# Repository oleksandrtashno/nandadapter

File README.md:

# 360-clip to Xgecu T48/T56 Adapter board
Adapter board to connect solderless TSSOP-56 clip (https://www.360-clip.com/) to Xgecu T48/T56 programmer.

The design was tested and funcitons properly.
## What you need to get it working

1. Xgecu T48/T56 programmer with USB cable
2. Original adapter board (comes with Xgecu programmer)
  NOTE: Now Xgecu programmer comes with different boards that are not compatible with this design, and the one that I have is apparently hard to find now
3. This adapter board with pins and sockets soldered.

Parts 4, 5 and 6 come with 360-clip.

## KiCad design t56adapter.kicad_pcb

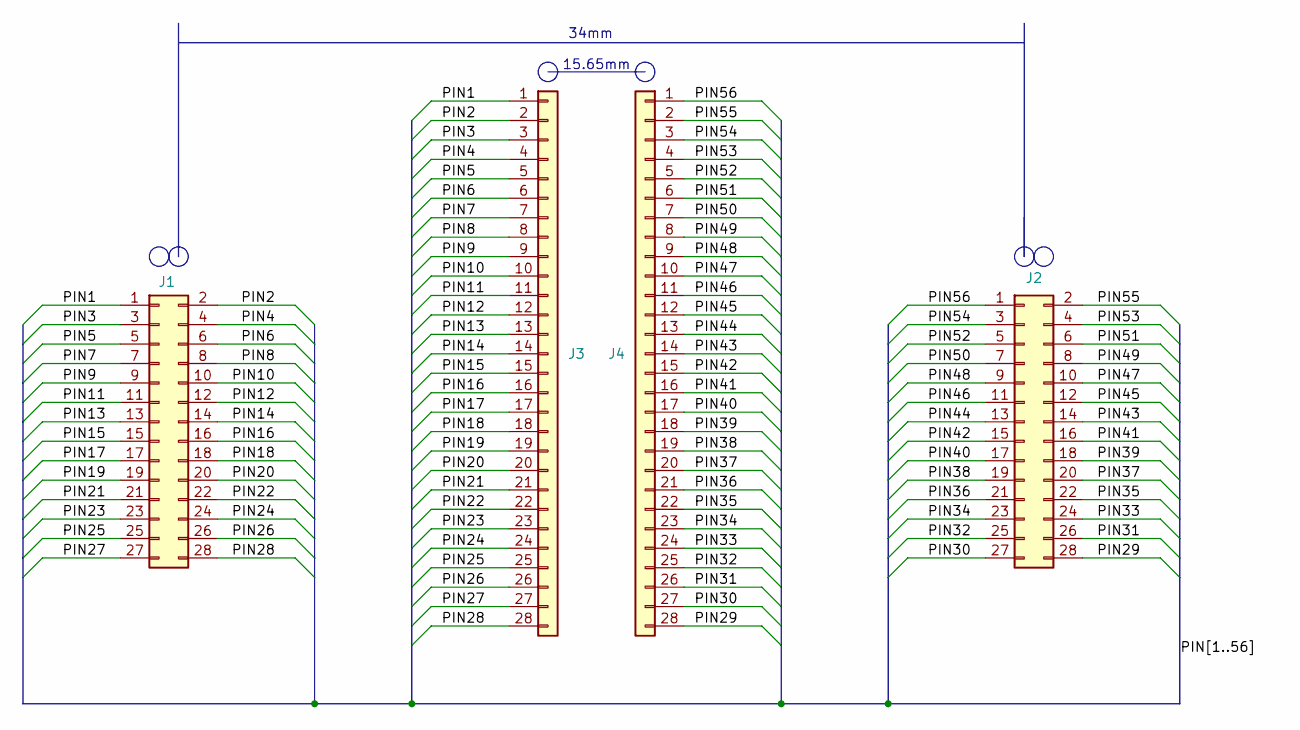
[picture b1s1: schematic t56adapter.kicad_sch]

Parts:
J1, J2: Conn_02x14_Odd_Even; PinHeader_2x14_P2.54mm_Vertical
J3, J4: Conn_01x28; PinHeader_1x28_P2.54mm_Vertical

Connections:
/PIN1: J1.1, J3.1
/PIN2: J1.2, J3.2
/PIN3: J1.3, J3.3
/PIN4: J1.4, J3.4
/PIN5: J1.5, J3.5
/PIN6: J1.6, J3.6
/PIN7: J1.7, J3.7
/PIN8: J1.8, J3.8
/PIN9: J1.9, J3.9
/PIN10: J1.10, J3.10
/PIN11: J1.11, J3.11
/PIN12: J1.12, J3.12
/PIN13: J1.13, J3.13
/PIN14: J1.14, J3.14
/PIN15: J1.15, J3.15
/PIN16: J1.16, J3.16
/PIN17: J1.17, J3.17
/PIN18: J1.18, J3.18
/PIN19: J1.19, J3.19
/PIN20: J1.20, J3.20
/PIN21: J1.21, J3.21
/PIN22: J1.22, J3.22
/PIN23: J1.23, J3.23
/PIN24: J1.24, J3.24
/PIN25: J1.25, J3.25
/PIN26: J1.26, J3.26
/PIN27: J1.27, J3.27
/PIN28: J1.28, J3.28
/PIN29: J2.28, J4.28
/PIN30: J2.27, J4.27
/PIN31: J2.26, J4.26
/PIN32: J2.25, J4.25
/PIN33: J2.24, J4.24
/PIN34: J2.23, J4.23
/PIN35: J2.22, J4.22
/PIN36: J2.21, J4.21
/PIN37: J2.20, J4.20
/PIN38: J2.19, J4.19
/PIN39: J2.18, J4.18
/PIN40: J2.17, J4.17
/PIN41: J2.16, J4.16
/PIN42: J2.15, J4.15
/PIN43: J2.14, J4.14
/PIN44: J2.13, J4.13
/PIN45: J2.12, J4.12
/PIN46: J2.11, J4.11
/PIN47: J2.10, J4.10
/PIN48: J2.9, J4.9
/PIN49: J2.8, J4.8
/PIN50: J2.7, J4.7
/PIN51: J2.6, J4.6
/PIN52: J2.5, J4.5
/PIN53: J2.4, J4.4
/PIN54: J2.3, J4.3
/PIN55: J2.2, J4.2
/PIN56: J2.1, J4.1

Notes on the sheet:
34mm
15.65mm

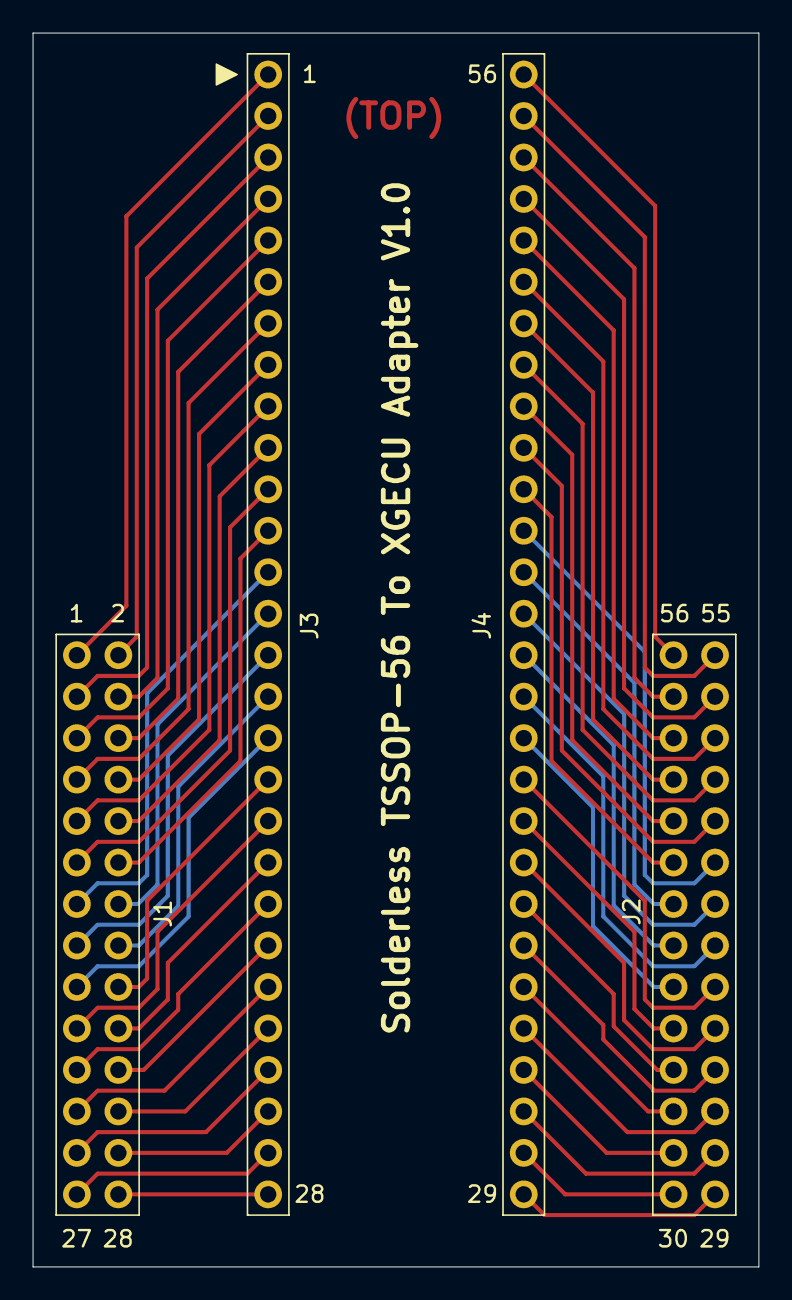
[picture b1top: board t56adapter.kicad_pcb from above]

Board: 2 copper layers, 44.5 x 75.6 mm, 4 parts (0 on the bottom side), 56 nets.

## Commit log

2024-08-17 created v1 gerber
